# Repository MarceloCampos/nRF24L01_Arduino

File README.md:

# nRF24L01_Arduino

by
http://marcelocampos.cc/

Placa projetada em KiCAD
https://kicad.org/

Pode ser utilizada com o excelente projeto IoT home Automation MySensors:
https://www.mysensors.org/hardware

---

---

---
Mod para medir bateria de alimentação

---
Mod para medir bateria de alimentação

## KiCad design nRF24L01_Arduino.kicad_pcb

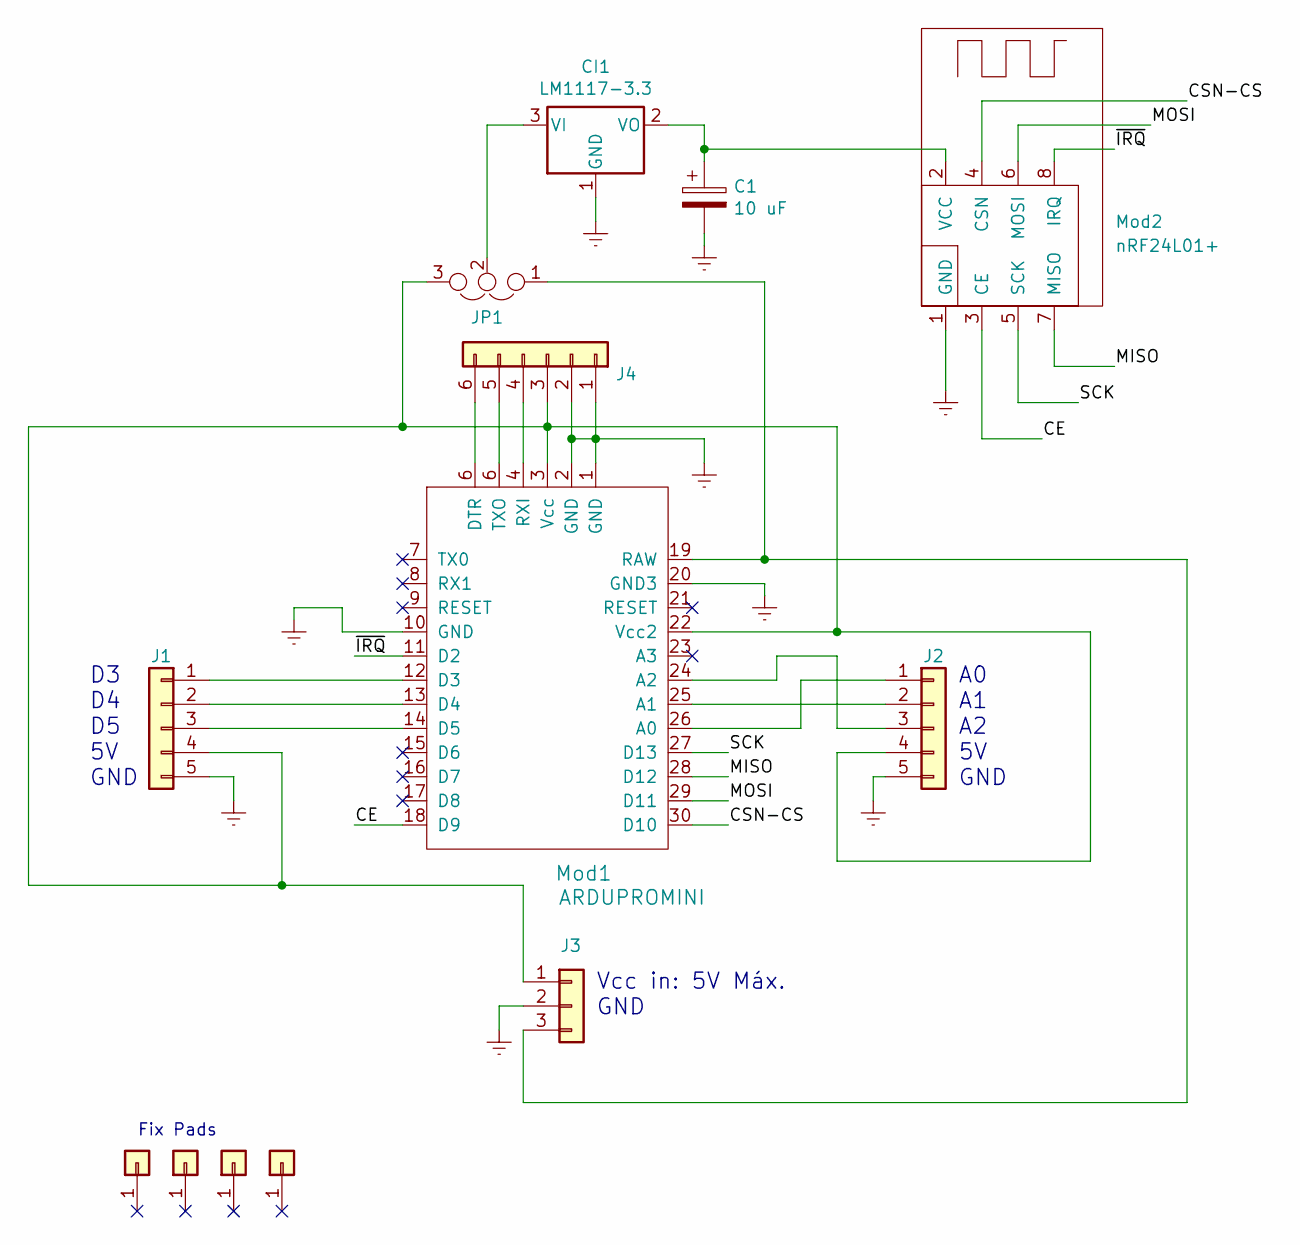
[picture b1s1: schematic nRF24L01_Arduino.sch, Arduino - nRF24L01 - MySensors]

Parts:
C1: 10 uF; CP_Radial_Tantal_D4.5mm_P2.50mm
CI1: LM1117-3.3; SOT-223-3_TabPin2
J1, J2: Conn_01x05; PinHeader_1x05_P2.54mm_Vertical
J3: Conn_01x03; PinHeader_1x03_P2.54mm_Vertical
J4: Conn_01x06; PinHeader_1x06_P2.54mm_Vertical
J11, J12, J13, J14: Conn_01x01; 1PAD
JP1: Jumper_NC_Dual; PinHeader_1x03_P2.54mm_Vertical
Mod1: ARDUPROMINI; ArduProMini
Mod2: nRF24L01+; PinHeader_2x04_P2.54mm_Vertical

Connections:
/CE: Mod1.18 (D9), Mod2.3 (CE)
/CSN-CS: Mod1.30 (D10), Mod2.4 (CSN)
/MISO: Mod1.28 (D12), Mod2.7 (MISO)
/MOSI: Mod1.29 (D11), Mod2.6 (MOSI)
/SCK: Mod1.27 (D13), Mod2.5 (SCK)
/~IRQ: Mod1.11 (D2), Mod2.8 (IRQ)
Earth: C1.2, CI1.1 (GND), J1.5, J2.5, J3.2, J4.1, J4.2, Mod1.1 (GND), Mod1.2 (GND), Mod1.10 (GND), Mod1.20 (GND3), Mod2.1 (GND)
unnamed: C1.1, CI1.2 (VO), Mod2.2 (VCC)
unnamed: CI1.3 (VI), JP1.2
unnamed: J1.1, Mod1.12 (D3)
unnamed: J1.2, Mod1.13 (D4)
unnamed: J1.3, Mod1.14 (D5)
unnamed: J1.4, J2.4, J3.1, J4.3, JP1.3, Mod1.3 (Vcc), Mod1.22 (Vcc2)
unnamed: J2.1, Mod1.26 (A0)
unnamed: J2.2, Mod1.25 (A1)
unnamed: J2.3, Mod1.24 (A2)
unnamed: J3.3, JP1.1, Mod1.19 (RAW)
unnamed: J4.4, Mod1.4 (RXI)

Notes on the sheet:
D3 D4 D5 5V GND
A0 A1 A2 5V GND
Vcc in: 5V Máx. GND
Fix Pads

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
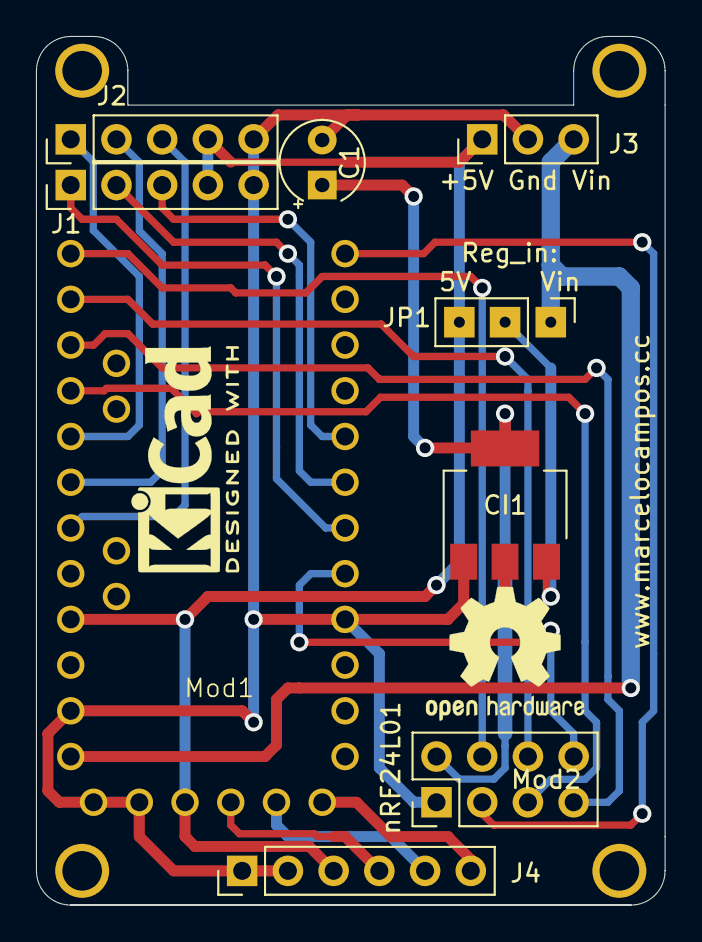
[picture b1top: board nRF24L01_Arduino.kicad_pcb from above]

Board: 2 copper layers, 34.9 x 48.3 mm, 13 parts (1 on the bottom side), 20 nets.

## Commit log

2021-03-28 Create none
2021-03-28 Add files via upload
    para produção
